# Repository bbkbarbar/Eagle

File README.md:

# Eagle folder to store eagle projects

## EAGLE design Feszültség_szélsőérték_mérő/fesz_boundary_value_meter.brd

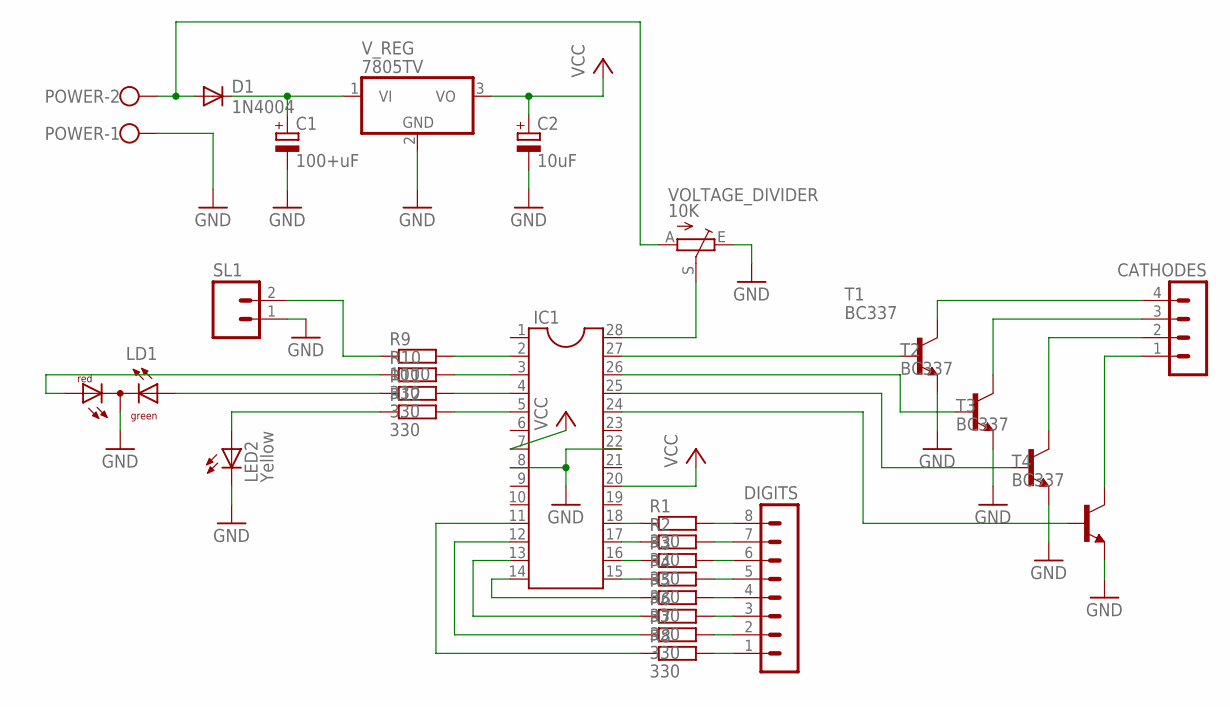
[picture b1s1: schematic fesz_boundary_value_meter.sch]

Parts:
C1: 100+uF; E2,5-6
C2: 10uF; E2,5-6E
CATHODES: MA04-1
D1: 1N4004; DO41-10
DIGITS: MA08-1
IC1: DIL28-3
LD1: DUOLED-RG-C; DUOLED-C-5MM
LED2: Yellow; LED3MM
POWER: W237-102
R1, R2, R3, R4, R5, R6, R7, R8, R10, R11, R12: 330; 0207/10
R9: 1000; 0207/10
SL1: MA02; 02PA
T1, T2, T3, T4: BC337; TO92
VOLTAGE_DIVIDER: 10K; S64W
V_REG: 7805TV; TO220V

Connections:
DIGIT_1_1: IC1.18, R1.1
DIGIT_2_: DIGITS.8, R1.2
DIGIT_2_1: IC1.17, R2.1
DIGIT_2_2: DIGITS.7, R2.2
DIGIT_3_1: IC1.16, R3.1
DIGIT_4_1: IC1.15, R4.1
DIGIT_5_1: IC1.14, R5.1
DIGIT_7_1: IC1.12, R7.1
DIGIT_8_1: IC1.11, R8.1
GND: C1.-, C2.-, IC1.8, IC1.22, LD1.C, LED2.K (C), POWER.1, SL1.1, T1.1 (E), T2.1 (E), T3.1 (E), T4.1 (E), VOLTAGE_DIVIDER.E, V_REG.2 (GND); also elsewhere on the board
unnamed: IC1.27, T1.2 (B)
unnamed: IC1.26, T2.2 (B)
unnamed: IC1.25, T3.2 (B)
unnamed: IC1.24, T4.2 (B)
unnamed: CATHODES.4, T1.3 (C)
unnamed: CATHODES.3, T2.3 (C)
unnamed: DIGITS.3, R6.2
unnamed: CATHODES.2, T3.3 (C)
unnamed: CATHODES.1, T4.3 (C)
unnamed: DIGITS.6, R3.2
unnamed: DIGITS.5, R4.2
unnamed: DIGITS.4, R5.2
unnamed: DIGITS.1, R8.2
unnamed 23: LD1.AR, R10.1; also elsewhere on the board
unnamed: IC1.28, VOLTAGE_DIVIDER.S
unnamed: IC1.13, R6.1
unnamed: DIGITS.2, R7.2
unnamed: IC1.2, R9.2
unnamed: IC1.3, R10.2
unnamed: R9.1, SL1.2
unnamed 30: LED2.A, R12.1; also elsewhere on the board
unnamed: IC1.4, R11.2
unnamed: IC1.5, R12.2
unnamed: LD1.AX (AG), R11.1
VCC: C2.+, IC1.7, IC1.20, V_REG.3 (VO)
V_IN_MEASURE: D1.A, POWER.2, VOLTAGE_DIVIDER.A
V_IN_SUPPLY: C1.+, D1.C, V_REG.1 (VI)

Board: 2 copper layers, 29 parts (0 on the bottom side), 37 nets, no tracks yet.

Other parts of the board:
LD2: DUOLED-C-5MM

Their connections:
GND: LD2.C; also elsewhere on the board
unnamed 23: LD2.AR; also elsewhere on the board
unnamed 30: LD2.AX; also elsewhere on the board

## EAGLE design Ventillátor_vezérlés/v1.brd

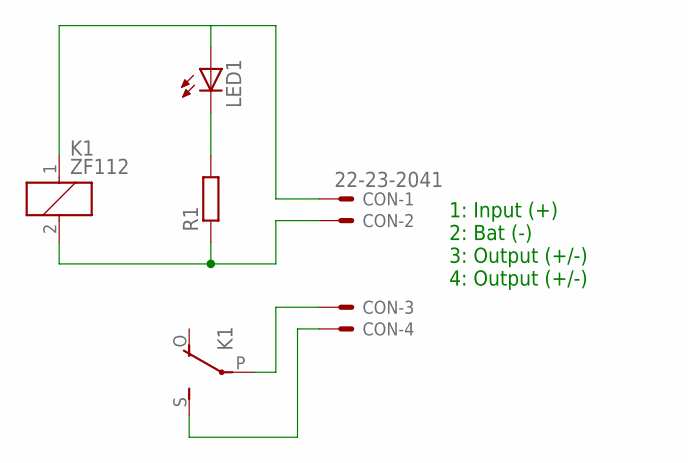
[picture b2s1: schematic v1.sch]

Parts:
CON: 22-23-2041
K1: ZF112
LED1: LED3MM
R1: R-EU_0207/12; 0207/12

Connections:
GND: CON.2, K1.2, R1.1
unnamed: LED1.K (C), R1.2
OUTPUT1: CON.3, K1.P
OUTPUT2: CON.4, K1.S
SWITCHED: CON.1, K1.1, LED1.A

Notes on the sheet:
1: Input (+) 2: Bat (-) 3: Output (+/-) 4: Output (+/-)

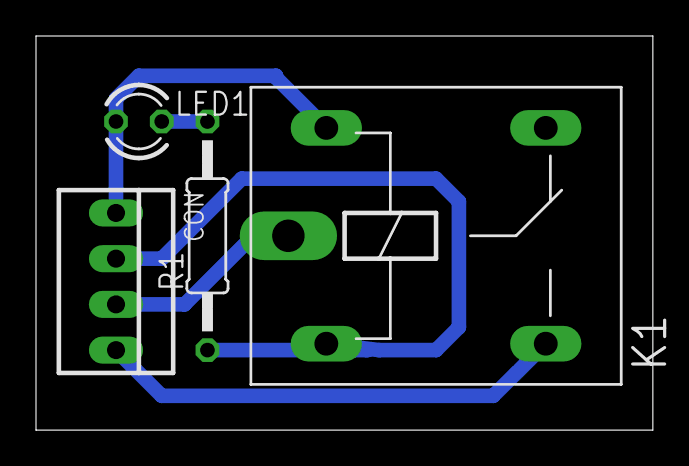
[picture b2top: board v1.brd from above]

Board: 2 copper layers, 34.3 x 21.9 mm, 4 parts (0 on the bottom side), 5 nets.

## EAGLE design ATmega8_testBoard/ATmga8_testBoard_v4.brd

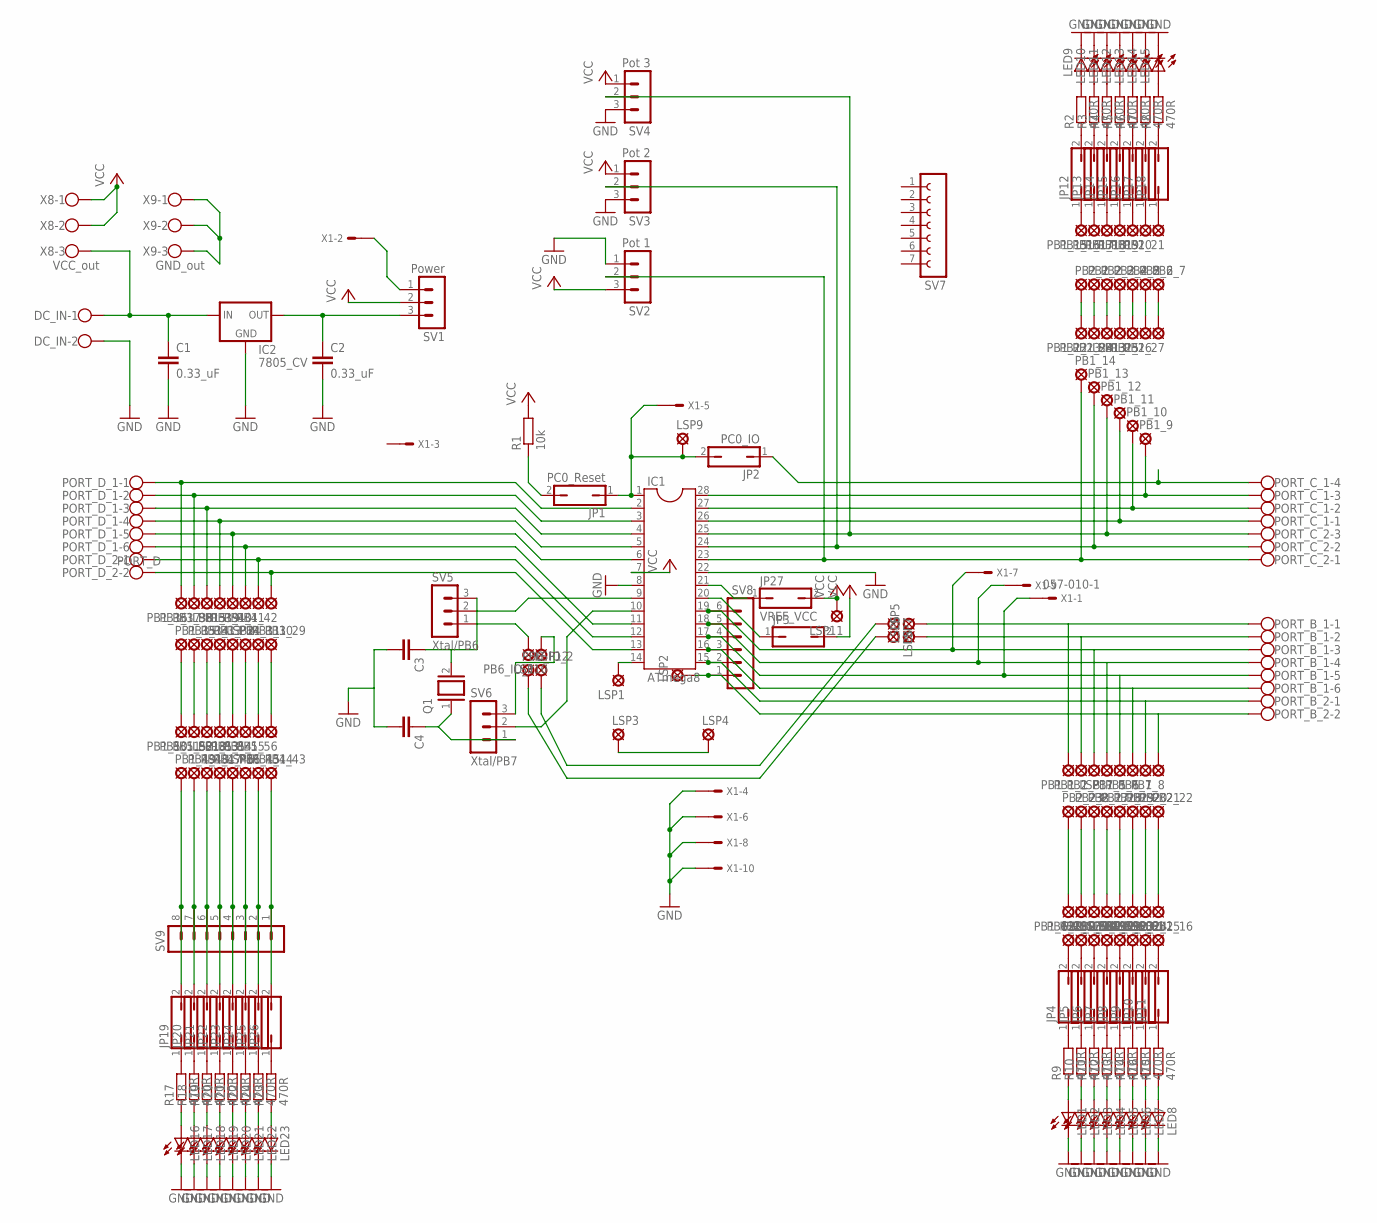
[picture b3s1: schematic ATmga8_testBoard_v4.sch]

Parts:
C1, C2: 0.33_uF; C5B2.5
C3, C4: C-EU025-024X044; C025-024X044
DC_IN: W237-102
IC1: ATmega8; DIL28-3
IC2: 7805_CV; 78XXS
JP1: PC0_Reset; JP1
JP2: PC0_IO; JP1
JP3, JP4, JP5, JP6, JP7, JP8, JP9, JP10, JP11, JP12, JP13, JP14, JP15, JP16, JP17, JP18, JP19, JP20, JP21, JP22, JP23, JP24, JP25, JP26: JP1Q; JP1
JP27: VREF_VCC; JP1
LED1, LED2, LED3, LED4, LED5, LED6, LED7, LED8, LED9, LED10, LED11, LED12, LED13, LED14, LED15, LED16, LED17, LED18, LED19, LED20, LED21, LED22, LED23: LED3MM
LSP1, LSP2, LSP3, LSP4, LSP5, LSP6, LSP7, LSP8, LSP9, LSP10, LSP11, LSP12, LSP13, LSP14, LSP15, LSP16, LSP17, LSP18, LSP19: LSP10
PB1_1, PB1_2, PB1_3, PB1_5, PB1_6, PB1_7, PB1_8, PB1_9, PB1_10, PB1_11, PB1_12, PB1_13, PB1_14, PB1_15, PB1_16, PB1_17, PB1_18, PB1_19, PB1_20, PB1_21, PB1_22, PB1_23, PB1_24, PB1_25, PB1_26, PB1_27, PB1_28, PB1_29, PB1_30, PB1_31, PB1_32, PB1_33, PB1_34, PB1_35, PB1_36, PB1_37, PB1_38, PB1_39, PB1_40, PB1_41, PB1_42, PB1_43, PB1_44, PB1_45, PB1_46, PB1_47, PB1_48, PB1_49, PB1_50, PB1_51, PB1_52, PB1_53, PB1_54, PB1_55, PB1_56, PB1_57, PB1_58, PB1_59, PB1_60, PB1_61, PB1_62, PB2_1, PB2_2, PB2_3, PB2_4, PB2_5, PB2_6, PB2_7, PB2_8, PB2_9, PB2_10, PB2_11, PB2_12, PB2_13, PB2_14, PB2_15, PB2_16, PB2_17, PB2_18, PB2_19, PB2_20, PB2_21, PB2_22, PB2_23, PB6_IO_1, PB6_IO_2: LSP10
PORT_B_1: W237-6
PORT_B_2: W237-102
PORT_C_1: W237-4
PORT_C_2: W237-103
PORT_D_1: PORT_D; W237-6
PORT_D_2: W237-102
Q1: XTAL; Q
R1: 10k; 0204/7
R2, R3, R4, R5, R6, R7, R8, R9, R10, R11, R12, R13, R14, R15, R16, R17, R18, R19, R20, R21, R22, R23, R24: 470R; 0207/7
SV1: Power; MA03-1
SV2: Pot 1; MA03-1
SV3: Pot 2; MA03-1
SV4: Pot 3; MA03-1
SV5: Xtal/PB6; MA03-1
SV6: Xtal/PB7; MA03-1
SV7: FE07-1; FE07
SV8: MA06-1
SV9: MA08-1
X1: 057-010-1
X8: VCC_out; W237-103
X9: GND_out; W237-103

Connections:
AVCC: IC1.19, PB1_3.MP, PORT_B_1.3, SV8.6, X1.7
unnamed: C2.1, IC2.OUT, SV1.3
unnamed: C1.1, DC_IN.1, IC2.IN, X8.3
unnamed: IC1.1, JP1.1, JP2.2, LSP9.MP, X1.5
unnamed: IC1.14, LSP1.MP
unnamed: LSP3.MP, LSP4.MP
unnamed: PB1_22.MP, PB2_1.MP
unnamed: PB1_23.MP, PB2_2.MP
unnamed: PB1_24.MP, PB2_3.MP
unnamed: LSP13.MP, PB2_4.MP
unnamed: LSP8.MP, PB6_IO_2.MP
unnamed: IC1.20, JP3.1
unnamed: LSP7.MP, LSP12.MP
unnamed: IC1.23, PB1_14.MP, PORT_C_2.1, SV2.2
unnamed: IC1.24, PB1_13.MP, PORT_C_2.2, SV3.2
unnamed: IC1.26, PB1_11.MP, PORT_C_1.1
unnamed: IC1.27, PB1_10.MP, PORT_C_1.2
unnamed: IC1.28, PB1_9.MP, PORT_C_1.3
unnamed: JP2.1, PORT_C_1.4
unnamed: JP1.2, R1.1
unnamed: PB1_25.MP, PB2_5.MP
unnamed: PB1_26.MP, PB2_6.MP
unnamed: IC1.10, SV6.2
unnamed: IC1.9, SV5.2
unnamed: IC1.2, PB1_36.MP, PORT_D_1.1
unnamed: IC1.3, PB1_37.MP, PORT_D_1.2
unnamed: IC1.4, PB1_38.MP, PORT_D_1.3
unnamed: IC1.5, LSP15.MP, PORT_D_1.4
unnamed: IC1.6, PB1_39.MP, PORT_D_1.5
unnamed: PB1_28.MP, PB2_8.MP
unnamed: C4.1, Q1.1, SV6.1
unnamed: C3.1, Q1.2, SV5.3
unnamed: LSP10.MP, SV6.3
unnamed: PB6_IO_1.MP, SV5.1
unnamed: IC1.11, PB1_40.MP, PORT_D_1.6
unnamed: IC1.12, PB1_41.MP, PORT_D_2.1
unnamed: IC1.13, PB1_42.MP, PORT_D_2.2
unnamed: IC1.18, LSP17.MP, PORT_B_1.4, SV8.5, X1.9
unnamed: IC1.17, PB1_5.MP, PORT_B_1.5, SV8.4, X1.1
unnamed: IC1.16, PB1_6.MP, PORT_B_1.6, SV8.3
unnamed: IC1.15, PB1_7.MP, PORT_B_2.1, SV8.2
unnamed: LSP2.MP, PB1_8.MP, PORT_B_2.2, SV8.1
unnamed: PB1_27.MP, PB2_7.MP
unnamed: IC1.21, JP27.1
unnamed: JP4.1, R9.2
unnamed: JP5.1, R10.2
unnamed: JP6.1, R11.2
unnamed: JP7.1, R12.2
unnamed: JP13.1, PB1_16.MP
unnamed: JP9.1, R14.2
unnamed: JP11.1, R15.2
unnamed: JP10.1, R16.2
unnamed: LED9.A, R2.2
unnamed: JP14.1, PB1_17.MP
unnamed: JP15.1, PB1_18.MP
unnamed: JP17.2, R7.1
unnamed: JP17.1, PB1_20.MP
unnamed: JP18.1, PB1_21.MP
unnamed: JP12.2, R2.1
unnamed: JP14.2, R4.1
unnamed: JP16.2, R6.1
unnamed: JP13.2, R3.1
unnamed: JP18.2, R8.1
unnamed: LED1.A, R9.1
unnamed: LED2.A, R10.1
unnamed: LED3.A, R11.1
unnamed: LED4.A, R12.1
unnamed: LED5.A, R13.1
unnamed: LED7.A, R16.1
unnamed: LED6.A, R14.1
unnamed: LED8.A, R15.1
unnamed: LED10.A, R3.2
unnamed: LED11.A, R4.2
unnamed: LED12.A, R5.2
unnamed: LED13.A, R6.2
unnamed: LED14.A, R7.2
unnamed: LED15.A, R8.2
unnamed: JP4.2, PB2_9.MP
unnamed: JP5.2, PB2_10.MP
unnamed: JP7.2, PB2_12.MP
unnamed: JP8.2, PB2_13.MP
unnamed: JP9.2, PB2_14.MP
unnamed: JP10.2, PB2_15.MP
unnamed: PB1_35.MP, PB1_50.MP
unnamed: PB1_34.MP, PB1_51.MP
unnamed: PB1_33.MP, PB1_52.MP
unnamed: LSP18.MP, PB1_32.MP
unnamed: LSP14.MP, PB1_53.MP
unnamed: PB1_31.MP, PB1_54.MP
unnamed: PB1_30.MP, PB1_55.MP
unnamed: PB1_29.MP, PB1_56.MP
unnamed: JP19.1, R17.2
unnamed: JP20.1, R18.2
unnamed: JP21.1, R19.2
unnamed: JP23.1, R21.2
unnamed: JP24.1, R22.2
unnamed: JP25.1, R24.2
unnamed: LED16.A, R17.1
unnamed: LED17.A, R18.1
unnamed: LED18.A, R19.1
unnamed: LED19.A, R20.1
unnamed: LED20.A, R21.1
unnamed: LED22.A, R24.1
unnamed: LED21.A, R22.1
unnamed: LED23.A, R23.1
unnamed: JP20.2, PB1_48.MP, SV9.7
unnamed: JP21.2, PB1_47.MP, SV9.6
unnamed: JP22.2, PB1_46.MP, SV9.5
unnamed: JP24.2, PB1_45.MP, SV9.3
unnamed: JP25.2, PB1_44.MP, SV9.2
unnamed: JP26.2, PB1_43.MP, SV9.1
unnamed: PB1_57.MP, PB2_17.MP
unnamed: PB1_58.MP, PB2_18.MP
unnamed: LSP19.MP, PB2_19.MP
unnamed: PB1_59.MP, PB2_20.MP
unnamed: PB1_60.MP, PB2_21.MP
unnamed: PB1_61.MP, PB2_22.MP
unnamed: PB1_62.MP, PB2_23.MP
unnamed: X9.1, X9.2, X9.3
unnamed: C1.2, C2.2, C3.2, C4.2, DC_IN.2, IC1.8, IC1.22, IC2.GND, LED1.K (C), LED2.K (C), LED3.K (C), LED4.K (C), LED5.K (C), LED6.K (C), LED7.K (C), LED8.K (C), LED9.K (C), LED10.K (C), LED11.K (C), LED12.K (C), LED13.K (C), LED14.K (C), LED15.K (C), LED16.K (C), LED17.K (C), LED18.K (C), LED19.K (C), LED20.K (C), LED21.K (C), LED22.K (C), LED23.K (C), SV2.1, SV3.3, SV4.3, X1.4, X1.6, X1.8, X1.10
unnamed: SV1.1, X1.2
unnamed: JP23.2, LSP16.MP, SV9.4
unnamed: IC1.25, PB1_12.MP, PORT_C_2.3, SV4.2
unnamed: JP8.1, R13.2
unnamed: JP16.1, PB1_19.MP
unnamed: JP11.2, PB2_16.MP
unnamed: JP15.2, R5.1
unnamed: JP12.1, PB1_15.MP
unnamed: JP6.2, PB2_11.MP
unnamed: LSP6.MP, PB1_2.MP, PORT_B_1.2
unnamed: JP26.1, R23.2
unnamed: JP22.1, R20.2
unnamed: JP19.2, PB1_49.MP, SV9.8
unnamed: LSP5.MP, PB1_1.MP, PORT_B_1.1
VCC: IC1.7, JP3.2, JP27.2, LSP11.MP, R1.2, SV1.2, SV2.3, SV3.1, SV4.1, X8.1, X8.2

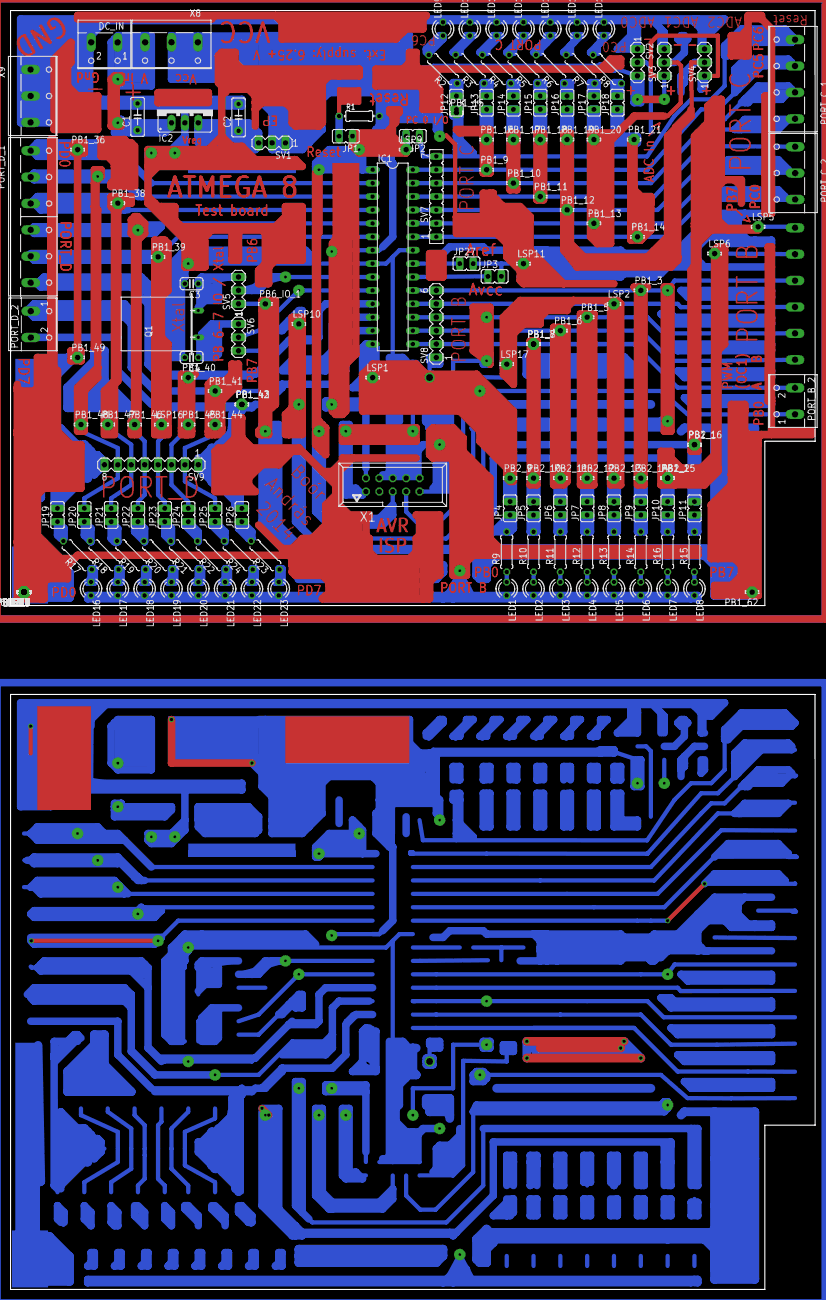
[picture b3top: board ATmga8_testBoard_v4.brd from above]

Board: 2 copper layers, 152.4 x 112.7 mm, 205 parts (1 on the bottom side), 135 nets.

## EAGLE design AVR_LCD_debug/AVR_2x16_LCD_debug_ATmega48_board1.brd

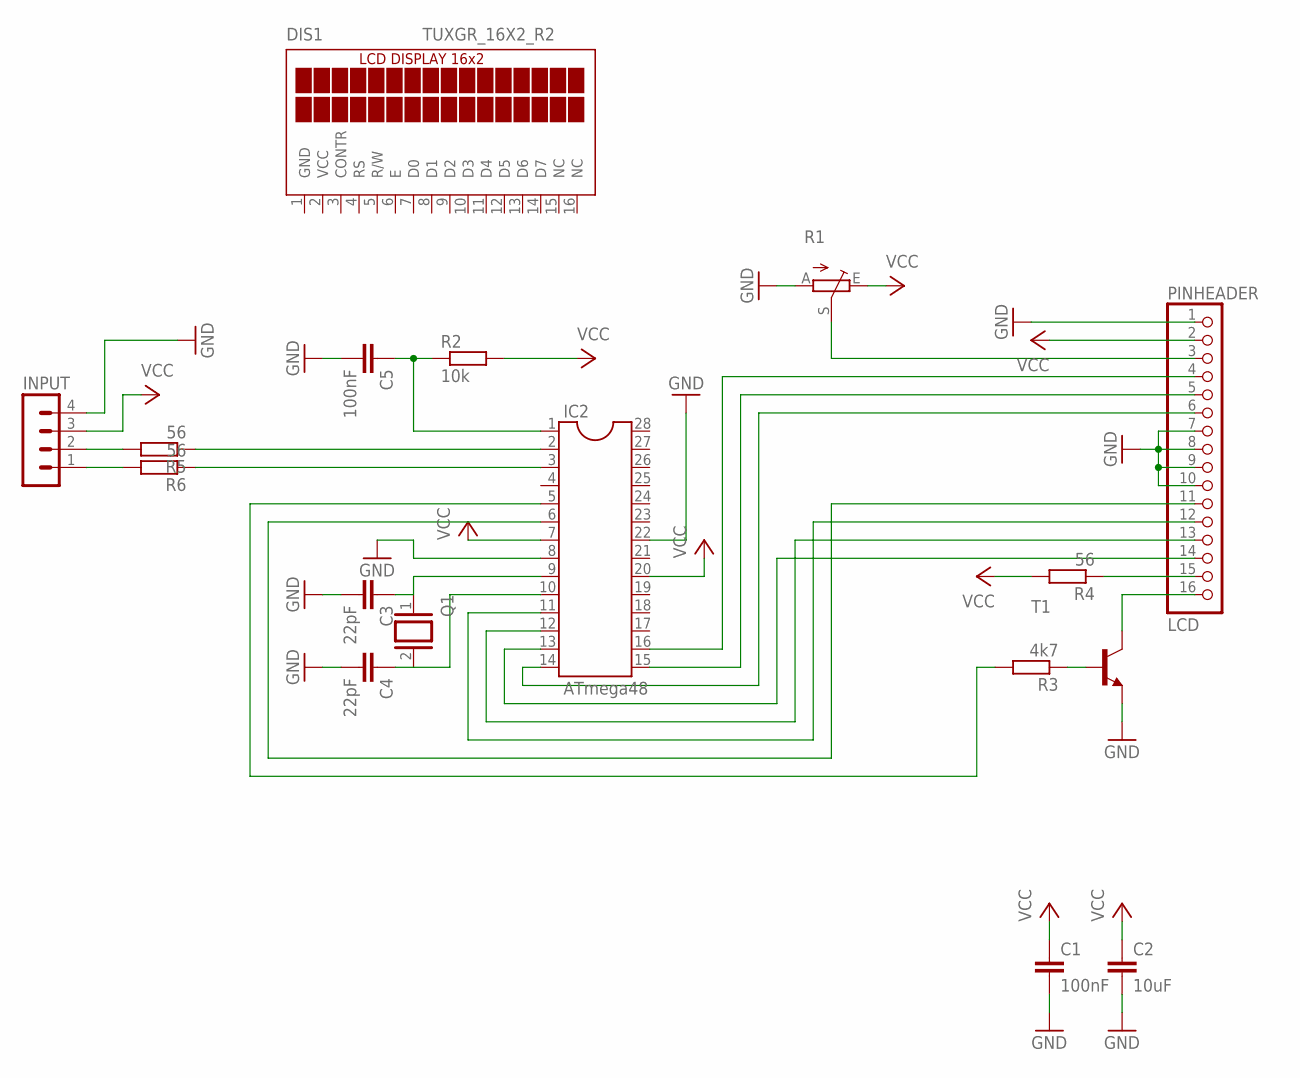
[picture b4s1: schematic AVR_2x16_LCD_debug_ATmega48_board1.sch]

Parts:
C1, C5: 100nF; C5B2.5
C2: 10uF; C5B2.5
C3, C4: 22pF; C5B2.5
DIS1: TUXGR_16X2_R2
IC2: ATmega48; DIL28-3
INPUT: MA04-1
PINHEADER: LCD; 1X16
Q1: XTAL; Q
R1: TRIM_EU-CA6V; CA6V
R2: 10k; 0204/5
R3: 4k7; 0204/5
R4, R5, R6: 56; 0204/5
T1: -NPN-TO92; TO92

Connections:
GND: C1.2, C2.2, C3.2, C4.2, C5.2, DIS1.1 (GND), IC2.8, IC2.22, INPUT.4, PINHEADER.1, PINHEADER.7, PINHEADER.8, PINHEADER.9, PINHEADER.10, R1.A, T1.1 (E)
unnamed: PINHEADER.3, R1.S
unnamed: C3.1, IC2.9, Q1.1
unnamed: C4.1, IC2.10, Q1.2
unnamed: IC2.2, R5.1
unnamed: IC2.5, R3.2
unnamed: IC2.3, R6.1
unnamed: R3.1, T1.2 (B)
unnamed: PINHEADER.16, T1.3 (C)
unnamed: PINHEADER.15, R4.1
unnamed: IC2.16, PINHEADER.4
unnamed: IC2.15, PINHEADER.5
unnamed: IC2.14, PINHEADER.6
unnamed: IC2.13, PINHEADER.14
unnamed: IC2.12, PINHEADER.13
unnamed: IC2.11, PINHEADER.12
unnamed: IC2.6, PINHEADER.11
RESET: C5.1, IC2.1, R2.1
RX: INPUT.2, R5.2
TX: INPUT.1, R6.2
VCC: C1.1, C2.1, DIS1.2 (VCC), IC2.7, IC2.20, INPUT.3, PINHEADER.2, R1.E, R2.2, R4.2

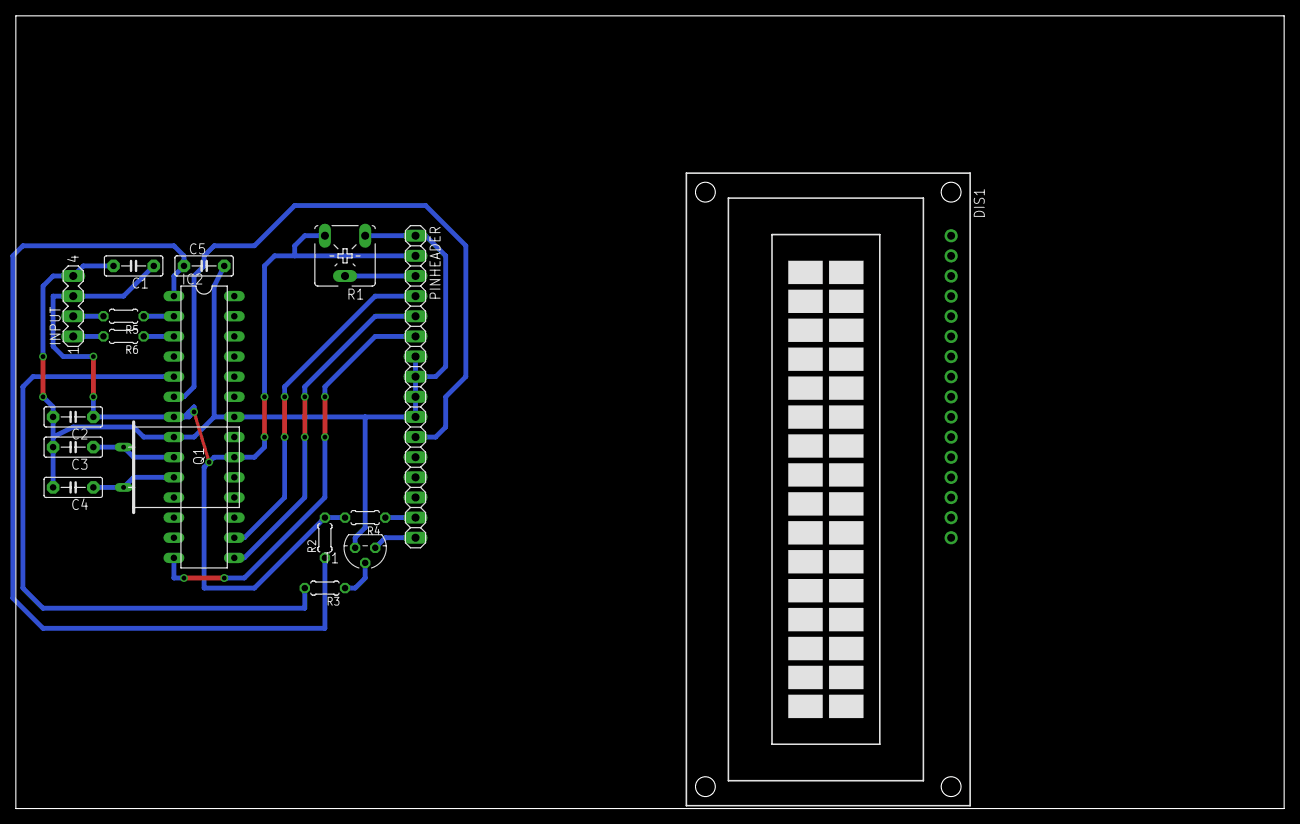
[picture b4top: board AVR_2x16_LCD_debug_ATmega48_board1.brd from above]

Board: 2 copper layers, 160.0 x 100.0 mm, 17 parts (0 on the bottom side), 21 nets.

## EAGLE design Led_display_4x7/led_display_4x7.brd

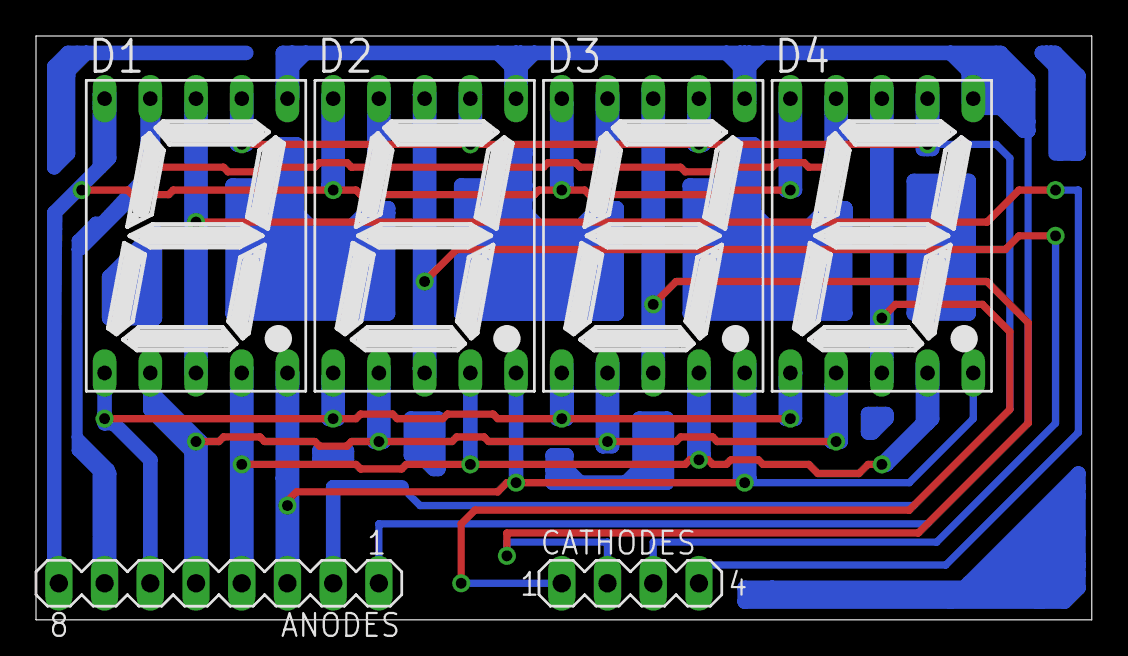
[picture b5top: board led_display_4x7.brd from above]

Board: 2 copper layers, 58.7 x 32.4 mm, 6 parts (0 on the bottom side), 12 nets.

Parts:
ANODES: MA08-1
CATHODES: MA04-1
D1, D2, D3, D4: 7SEG-13

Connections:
F: ANODES.7, D1.9, D2.9, D3.9, D4.9
G: ANODES.8, D1.10, D2.10, D3.10, D4.10
unnamed: ANODES.5, D1.2, D2.2, D3.2, D4.2
unnamed: ANODES.6, D1.1, D2.1, D3.1, D4.1
unnamed: ANODES.4, D1.4, D2.4, D3.4, D4.4
unnamed: ANODES.2, D1.7, D2.7, D3.7, D4.7
unnamed: ANODES.1, D1.6, D2.6, D3.6, D4.6
unnamed: CATHODES.1, D4.3, D4.8
unnamed: CATHODES.2, D3.3, D3.8
unnamed: CATHODES.3, D2.3, D2.8
unnamed: CATHODES.4, D1.3, D1.8
POINT: ANODES.3, D1.5, D2.5, D3.5, D4.5

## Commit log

2016-04-12 Initital commit for Eagle folder
2016-04-12 Add gitIgnore
2016-04-12 Remove *.b|s#?
2016-04-12 v2 added
2016-04-16 Resistor added for base pins of transistors. + filled PCB created.
